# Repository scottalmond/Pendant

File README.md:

# Pendant

The purpose of this project is to develop a piece of artisan eletronics to serve as a prize for an eletronics competition.  The design consists of a PCB and 3D-printed case.  The CAD model for the case has been excluded from this project because it incorporates proprietary elements.

Development Tools
Arduino IDE
KiCAD
FreeCAD

The J3 header has a 1:1 pinout matching the Attiny85 processor.
Instructions for programming the Attiny85 using an Arduino is documented at the start of the Arduino code.  Once the Arduino has been programmed with the ArduinoAsISP program, it can be connected to the J3 programming header using the following connections:
https://hackster.imgix.net/uploads/cover_image/file/50546/Programming%20ATtiny85%20with%20Arduino%20Uno_bb.png?auto=compress%2Cformat&w=900&h=675&fit=min

License
CC BY 4.0: Scott Almond
https://creativecommons.org/licenses/by/4.0/

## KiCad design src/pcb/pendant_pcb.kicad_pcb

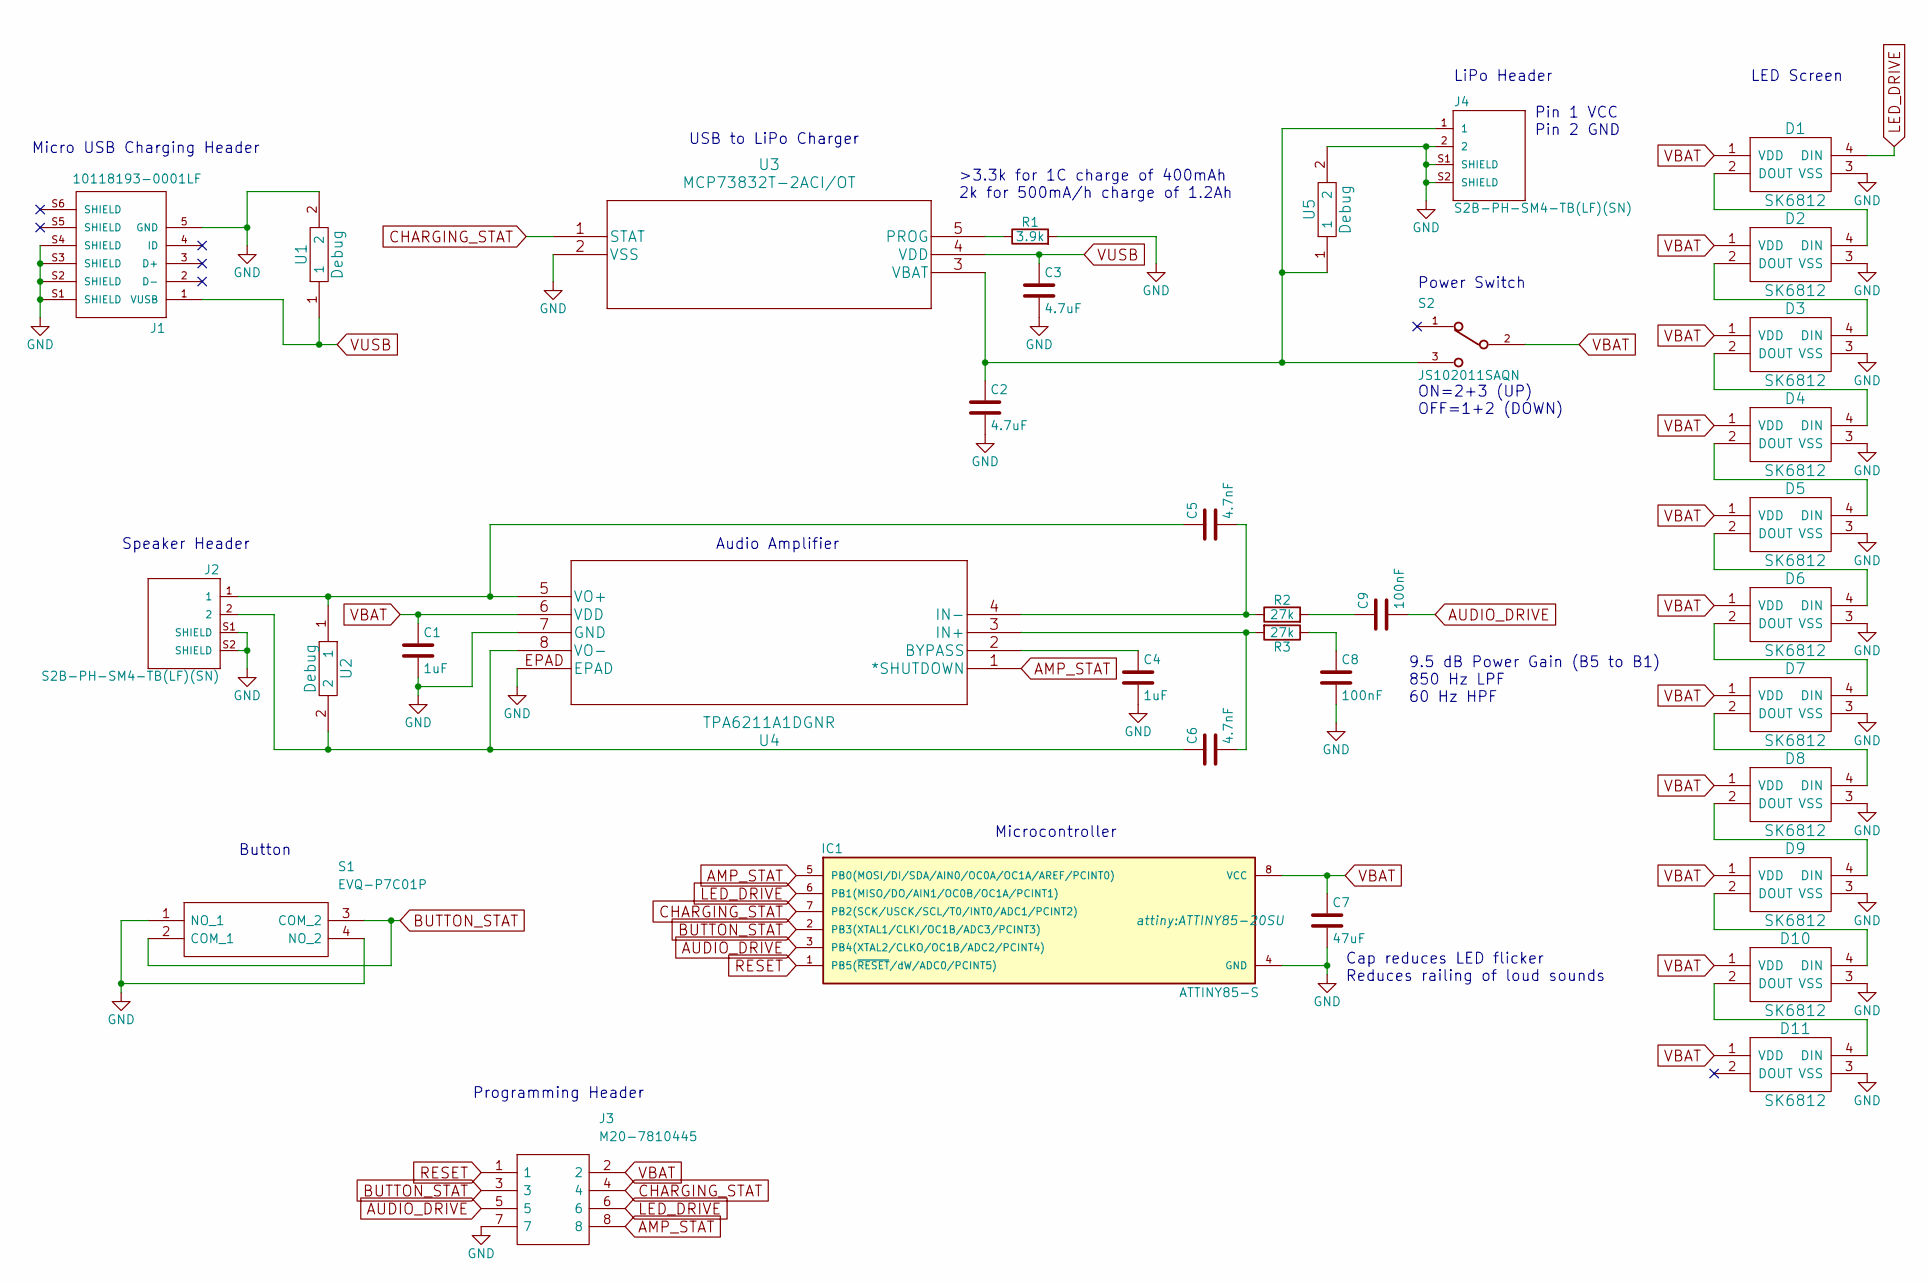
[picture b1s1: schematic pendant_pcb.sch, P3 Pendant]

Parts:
C1, C4: 1uF; C_0805
C2, C3: 4.7uF; C_0805
C5, C6: 4.7nF; C_0805
C7: 47uF; C_0805
C8, C9: 100nF; C_0805
D1, D2, D3, D4, D5, D6, D7, D8, D9, D10, D11: SK6812; LED_SK6812_PLCC4_5.0x5.0mm_P3.2mm
IC1: ATTINY85-S; ATTINY85-20SU
J1: 10118193-0001LF; FCI_10118193-0001LF
J2, J4: S2B-PH-SM4-TB(LF)(SN); JST_S2B-PH-SM4-TB(LF)(SN)
J3: M20-7810445; M207810445; Mouser Part Number 855-M20-7810445
R1: 3.9k; R_0805
R2, R3: 27k; R_0805
S1: EVQ-P7C01P; EVQP7C01P; Manufacturer_Part_Number EVQ-P7C01P; Mouser Part Number 667-EVQP7C01P
S2: JS102011SAQN; SW_JS102011SAQN
U1, U2, U5: Debug; Debug_2p
U3: MCP73832T-2ACI/OT; MCP73831T-2ACI&slash_OT
U4: TPA6211A1DGNR

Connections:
AMP_STAT: IC1.5 (PB0(MOSI/DI/SDA/AIN0/OC0A/OC1A/AREF/PCI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), J3.8, U4.1 (*SHUTDOWN)
AUDIO_DRIVE: C9.2, IC1.3 (PB4(XTAL2/CLKO/OC1B/ADC2/PCINT4)), J3.5
BUTTON_STAT: IC1.2 (PB3(XTAL1/CLKI/OC1B/ADC3/PCINT3)), J3.3, S1.2 (COM_1), S1.3 (COM_2)
CHARGING_STAT: IC1.7 (PB2(SCK/USCK/SCL/T0/INT0/ADC1/PCINT2)), J3.4, U3.1 (STAT)
GND: C1.2, C2.2, C3.2, C4.2, C7.2, C8.2, D1.3 (VSS), D2.3 (VSS), D3.3 (VSS), D4.3 (VSS), D5.3 (VSS), D6.3 (VSS), D7.3 (VSS), D8.3 (VSS), D9.3 (VSS), D10.3 (VSS), D11.3 (VSS), IC1.4 (GND), J1.5 (GND), J1.S1 (SHIELD), J1.S2 (SHIELD), J1.S3 (SHIELD), J1.S4 (SHIELD), J2.S1 (SHIELD), J2.S2 (SHIELD), J3.7, J4.2, J4.S1 (SHIELD), J4.S2 (SHIELD), R1.2, S1.1 (NO_1), S1.4 (NO_2), U1.2, U3.2 (VSS), U4.7 (GND), U4.EPAD, U5.2
LED_DRIVE: D1.4 (DIN), IC1.6 (PB1(MISO/DO/AIN1/OC0B/OC1A/PCINT1)), J3.6
unnamed: C2.1, J4.1, S2.3, U3.3 (VBAT), U5.1
unnamed: C4.1, U4.2 (BYPASS)
unnamed: C5.1, J2.1, U2.1, U4.5 (VO+)
unnamed: C5.2, R2.1, U4.4 (IN-)
unnamed: C6.1, J2.2, U2.2, U4.8 (VO-)
unnamed: C6.2, R3.2, U4.3 (IN+)
unnamed: C8.1, R3.1
unnamed: C9.1, R2.2
unnamed: D1.2 (DOUT), D2.4 (DIN)
unnamed: D2.2 (DOUT), D3.4 (DIN)
unnamed: D3.2 (DOUT), D4.4 (DIN)
unnamed: D4.2 (DOUT), D5.4 (DIN)
unnamed: D5.2 (DOUT), D6.4 (DIN)
unnamed: D6.2 (DOUT), D7.4 (DIN)
unnamed: D7.2 (DOUT), D8.4 (DIN)
unnamed: D8.2 (DOUT), D9.4 (DIN)
unnamed: D10.2 (DOUT), D11.4 (DIN)
unnamed: D9.2 (DOUT), D10.4 (DIN)
unnamed: R1.1, U3.5 (PROG)
RESET: IC1.1 (PB5(~RESET~/dW/ADC0/PCINT5)), J3.1
VBAT: C1.1, C7.1, D1.1 (VDD), D2.1 (VDD), D3.1 (VDD), D4.1 (VDD), D5.1 (VDD), D6.1 (VDD), D7.1 (VDD), D8.1 (VDD), D9.1 (VDD), D10.1 (VDD), D11.1 (VDD), IC1.8 (VCC), J3.2, S2.2, U4.6 (VDD)
VUSB: C3.1, J1.1 (VUSB), U1.1, U3.4 (VDD)

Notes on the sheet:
Pin 1 VCC Pin 2 GND
Programming Header
LiPo Header
Power Switch
USB to LiPo Charger
Audio Amplifier
Micro USB Charging Header
Speaker Header
LED Screen
ON=2+3 (UP) OFF=1+2 (DOWN)
Button
Microcontroller
>3.3k for 1C charge of 400mAh 2k for 500mA/h charge of 1.2Ah
9.5 dB Power Gain (B5 to B1) 850 Hz LPF 60 Hz HPF
Cap reduces LED flicker Reduces railing of loud sounds

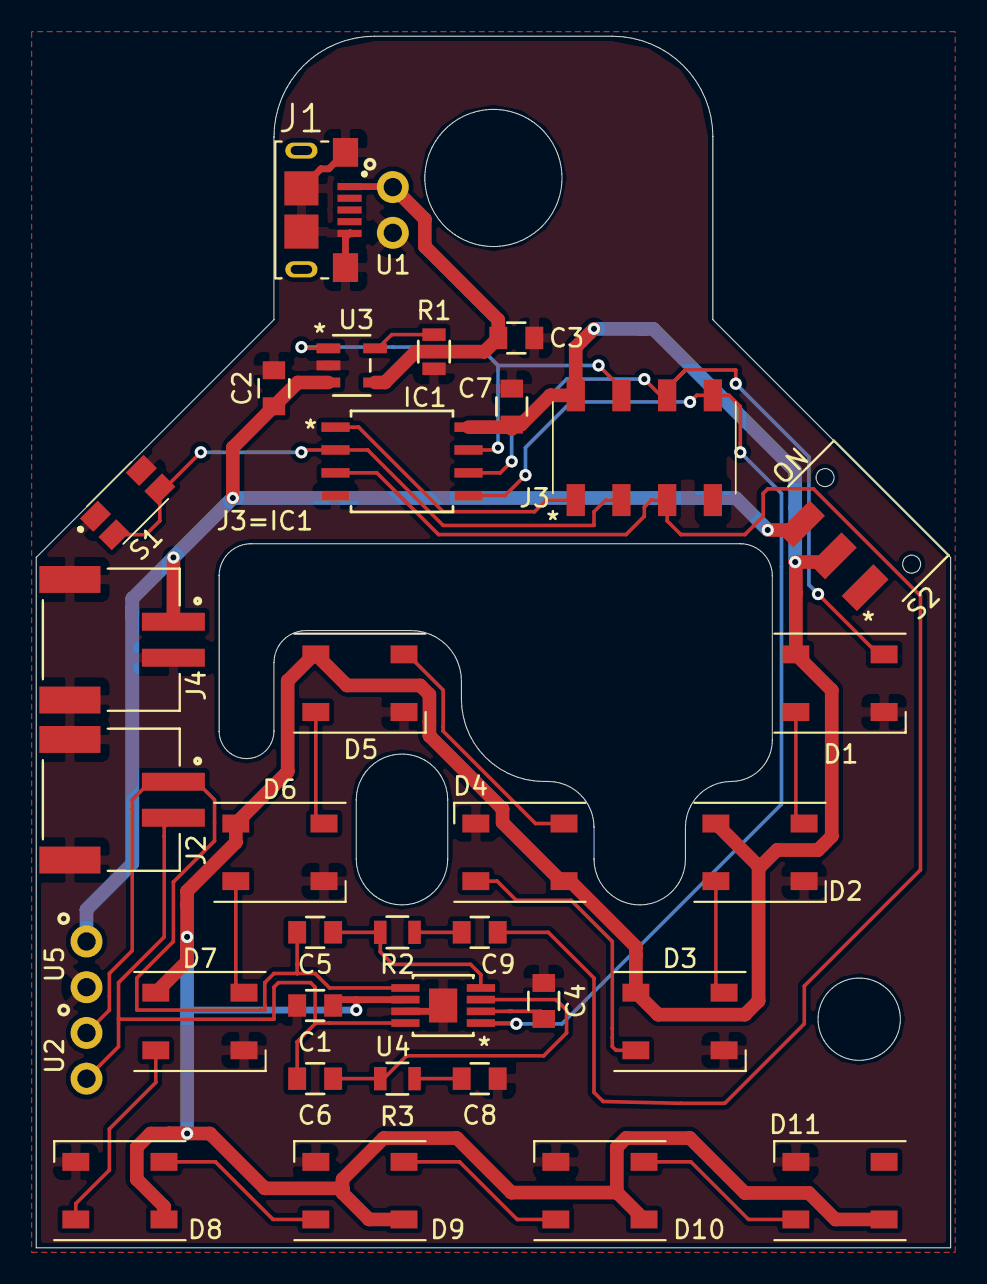
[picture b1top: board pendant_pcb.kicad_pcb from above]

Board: 2 copper layers, 50.8 x 67.3 mm, 35 parts (0 on the bottom side), 28 nets.

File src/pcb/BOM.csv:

For production run of 25 units,,,,,
,,,,,
Function,Qty,Unit Price,Extended Price,Part #,URL
JST Header,50,0.55,27.50,S2B-PH-SM4-TB(LF)(SN),https://www.digikey.com/product-detail/en/jst-sales-america-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
"LED, 10 pack",30,5.95,178.50,"2759, SK6812RGBW",https://www.digikey.com/product-detail/en/adafruit-industrie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
Processor,25,1.07,26.75,ATTINY85-20SU-ND,https://www.digikey.com/product-detail/en/ATTINY85-20SU/ATTI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
DC Power Switch,25,0.56,14.00,JS102011SAQN,https://www.digikey.com/product-detail/en/JS102011SAQN/401-1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
Button,25,0.37,9.25,EVQ-P7C01P,https://www.digikey.com/product-detail/en/EVQ-P7C01P/P16765C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
Battery 400mAh,25,4.95,123.75,PRT-13851,https://www.digikey.com/product-detail/en/PRT-13851/1568-149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
Speaker 8ohm,25,2.49,62.25,SP-4005-1,https://www.digikey.com/product-detail/en/SP-4005-1/433-1152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
Audio Amp,25,0.79,19.75,TPA6211A1DGNR,https://www.digikey.com/product-detail/en/TPA6211A1DGNR/296-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
Battery Charge Chip,25,0.48,12.00,MCP73832T-2ACI/OT,https://www.digikey.com/product-detail/en/microchip-technolo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
Program Header 2x4,25,1.17,29.25,M20-7810445,https://www.digikey.com/product-detail/en/M20-7810445/952-32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
USB Micro Header,25,0.38,9.50,10118193-0001LF,https://www.digikey.com/product-detail/en/10118193-0001LF/60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
3.9k Ohms,100,0.0085,0.85, RMCF0805JT3K90 ,https://www.digikey.com/product-detail/en/stackpole-electron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
27k Ohms,100,0.0085,0.85, RMCF0805JT27K0 ,https://www.digikey.com/product-detail/en/stackpole-electron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
"4.7 uF, ~4 micro",100,0.044,4.40, CL21A475KQFNNNG ,https://www.digikey.com/product-detail/en/samsung-electro-me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
"4.7 nF, ~4 nano",100,0.0238,2.38, CL21B472KBANNNC ,https://www.digikey.com/product-detail/en/samsung-electro-me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
"1 uF, 1 micro",100,0.0352,3.52, CL21B105KAFNNNE ,https://www.digikey.com/product-detail/en/samsung-electro-me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
"47 uF, ~40 micro",25,0.339,8.48, GRM21BC80G476ME15L ,https://www.digikey.com/product-detail/en/murata-electronics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
,,,,,
Unit Cost,,,21.32,,
Total Price,,,532.98,,

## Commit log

2019-05-06 push all resources

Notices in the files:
src/pcb/pendant_pcb.sch:
www.creativecommons.org/licenses/by/4.0
parts and their libraries:
Copyright 2016 Accelerated Designs. All rights reserved.
